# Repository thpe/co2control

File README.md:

# CO2 control
Monitor for CO2
## Features
 * EIA-485 interface
 * SCD-30 sensor
 * Input volatage 24 V
 * RP-2040
 * 4 LEDs
 * Relay
 * Oxygen Cell input < 150 mV (not yet tested)
 * 0-10 V output
 * 1 wire interface

## Issues and Limitations
The following issues with the current versions are known:
 * RX/TX to SCD30 need to be switched
 * doesn't connect via USB
   * USB C symbol should have been a receptable, not plug
   * Thus, B7/B6 are not connected to D+/-

## Connection
XLR male, pinout
 * 1. GND, Blue
 * 2. +24V, Blue/White
 * 3. 485A, Orange
 * 4. 485B, Orange/White

## Firmware
The [co2control-fw](https://github.com/thpe/co2control-fw) firmware samples the SCD-30 regulary and exposes the measurements via
modbus.

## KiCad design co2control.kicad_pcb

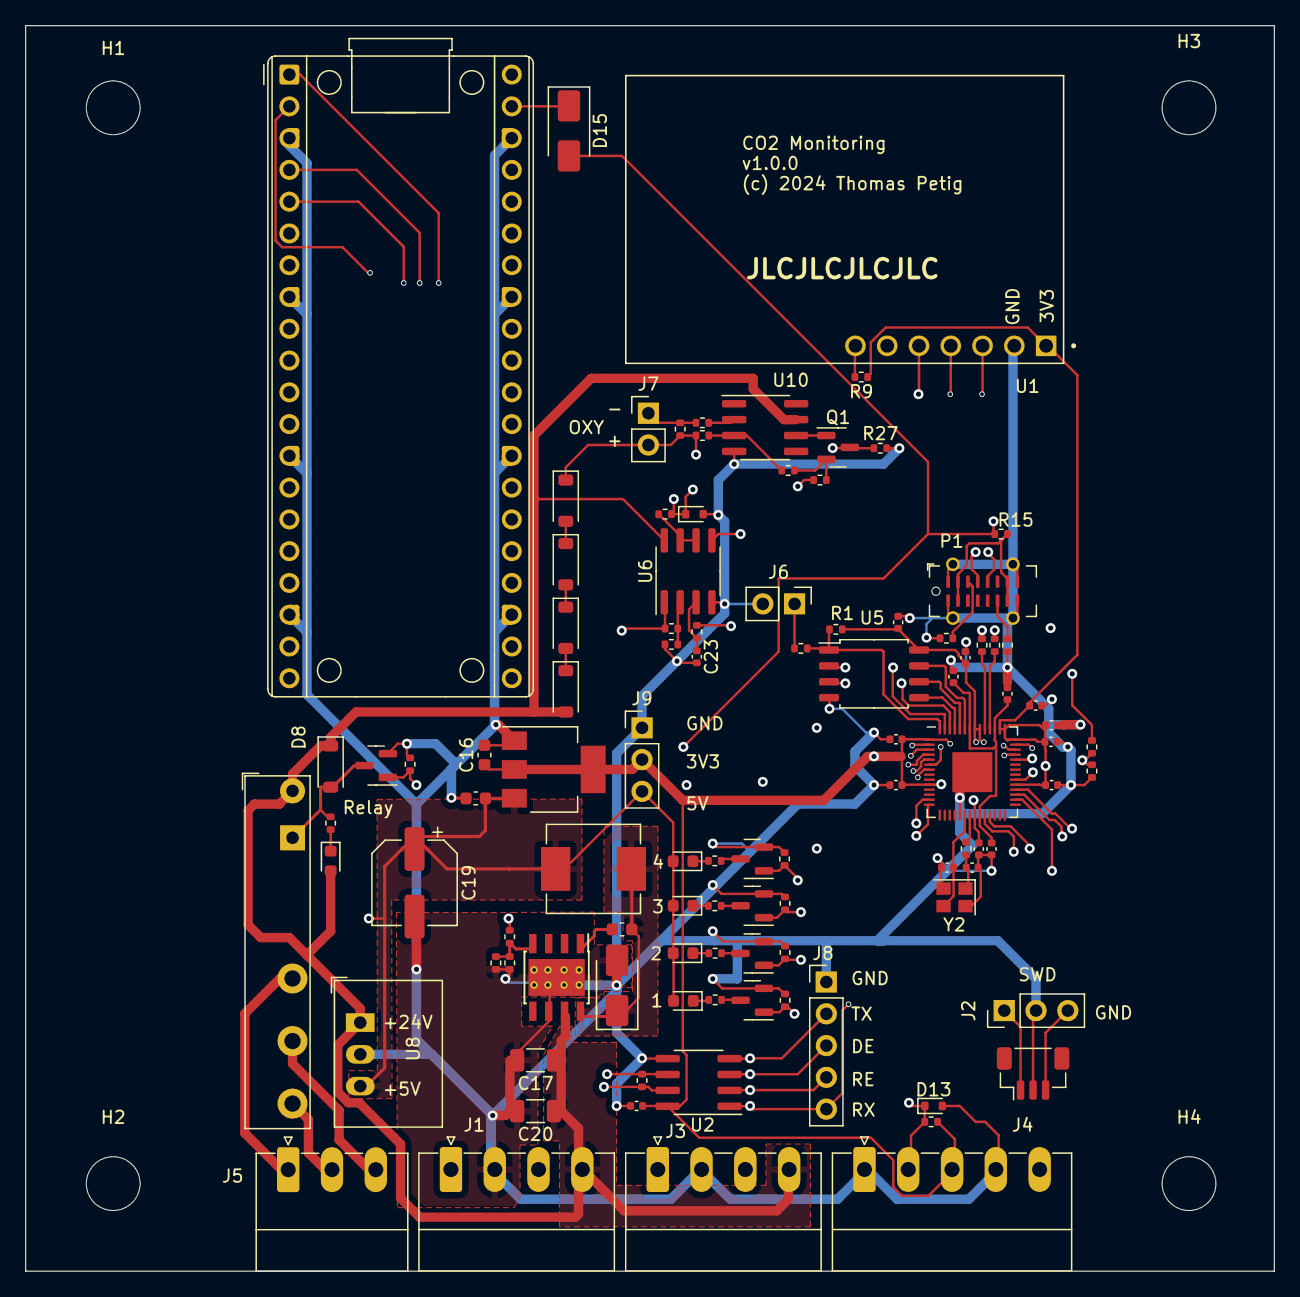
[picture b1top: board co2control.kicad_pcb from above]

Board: 4 copper layers, 99.8 x 99.6 mm, 106 parts (0 on the bottom side), 74 nets.

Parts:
C1, C4, C5, C6, C7, C8, C9, C10, C11, C12: 100n; C_0402_1005Metric
C2, C3, C23: 10p; C_0402_1005Metric
C13, C14: 1u; C_0402_1005Metric
C15, C16: 10u; C_0603_1608Metric
C17, C20: 4u7, 50V; C_1206_3216Metric
C18: 10n; C_0603_1608Metric
C19: 220u; CP_Elec_6.3x7.7
C21: 10n; C_0402_1005Metric
D2, D15: B340; D_SMA
D3, D4, D5, D6, D14: LED; LED_0603_1608Metric
D7, D8, D9, D10, D11: 1N4148W; D_SOD-123
D12, D13: MM5Z3V9; D_SOD-523
H1: MountingHole; MountingHole_4.3mm_M4_DIN965
H2, H3, H4: MountingHole; MountingHole_4.3mm_M4
J1, J3: Conn_01x04; PhoenixContact_MC_1,5_4-G-3.5_1x04_P3.50mm_Horizontal
J2: Conn_01x03_Pin; PinHeader_1x03_P2.54mm_Vertical
J4: Conn_01x05; PhoenixContact_MC_1,5_5-G-3.5_1x05_P3.50mm_Horizontal
J5: Conn_01x03; PhoenixContact_MC_1,5_3-G-3.5_1x03_P3.50mm_Horizontal
J6, J7: Conn_01x02; PinHeader_1x02_P2.54mm_Vertical
J8: Conn_01x05; PinHeader_1x05_P2.54mm_Vertical
J9: Conn_01x03; PinHeader_1x03_P2.54mm_Vertical
J10: Conn_01x03_Pin; JST_SH_BM03B-SRSS-TB_1x03-1MP_P1.00mm_Vertical
K1: Relay_SPDT; Relay_SPDT_Finder_34.51_Vertical
L1: 22u; L_Sunlord_MWSA0603S
P1: USB_C_Plug_USB2.0; USB_C_Receptacle_G-Switch_GT-USB-7051x
Q1: Q_PMOS_GSD; SOT-23
Q2, Q3, Q4, Q5, Q6: BSS138; SOT-23
R1, R15: DNF; R_0402_1005Metric
R2, R3, R16: 1k; R_0402_1005Metric
R4, R5: 27; R_0402_1005Metric
R6: 120; R_0402_1005Metric
R7, R9, R17, R19, R20, R27, R32, R33: 10k; R_0402_1005Metric
R8: 3k3; R_0402_1005Metric
R10, R12, R13, R30: 220; R_0402_1005Metric
R11, R22, R25, R26, R28, R29, R31, R36: 100k; R_0402_1005Metric
R14: 1M; R_0402_1005Metric
R18: 1k5; R_0402_1005Metric
R21: 4k7; R_0402_1005Metric
R23, R24: 330; R_0402_1005Metric
R34, R35: 5k1; R_0402_1005Metric
U1: SCD30; MODULE_SCD30
U2: SP3485EN; SOIC-8_3.9x4.9mm_P1.27mm
U3: AP1117-33; SOT-223-3_TabPin2
U4: RP2040; QFN-56-1EP_7x7mm_P0.4mm_EP3.2x3.2mm
U5: W25Q128JVS; SOIC-8_5.23x5.23mm_P1.27mm
U6: LM358; SOIC-8_3.9x4.9mm_P1.27mm
U7: RaspberryPi_Pico; RaspberryPi_Pico_Common_THT
U8: R-78C5.0-1.0; Converter_DCDC_RECOM_R-78E-0.5_THT
U9: TPS5430DDA; TI_SO-PowerPAD-8_ThermalVias
U10: OP07; SOIC-8_3.9x4.9mm_P1.27mm
Y2: 7E12000E10UCG; Crystal_SMD_2520-4Pin_2.5x2.0mm

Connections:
+1V1: C11.1, C12.1, C14.1, U4.23 (DVDD), U4.45 (VREG_VOUT), U4.50 (DVDD)
+3.3V: C1.1, C4.1, C5.1, C6.1, C7.1, C8.1, C9.1, C10.1, C13.1, C16.1, C21.1, J4.3, J9.2, R1.1, R9.1, R17.2, U1.1 (VDD), U2.8 (VCC), U3.2 (VO), U4.1 (IOVDD), U4.10 (IOVDD), U4.22 (IOVDD), U4.33 (IOVDD), U4.42 (IOVDD), U4.43 (ADC_AVDD), U4.44 (VREG_IN), U4.48 (USB_VDD), U4.49 (IOVDD), U5.8 (VCC)
+5V: C15.1, C19.1, D3.2 (A), D4.2 (A), D5.2 (A), D6.2 (A), D15.2 (A), J9.3, L1.2, R7.1, R15.2, R32.1, U3.3 (VI), U8.3 (OUT)
+24V: C17.1, C20.1, D7.2 (A), D8.1 (K), D14.2 (A), J1.4, J3.4, K1.A2, U6.8 (V+), U8.1 (IN), U9.7 (VIN), U10.7 (V+)
/io/1wire: D13.1 (K), J4.2, R17.1, U4.14 (GPIO11), U7.15 (GPIO11)
/io/485A: J1.1, J3.1, R6.1, U2.6 (A)
/io/485B: J1.3, J3.3, R6.2, U2.7 (B)
/io/MODBUS_DE: J8.3, U2.3 (DE), U4.4 (GPIO2), U7.4 (GPIO2)
/io/MODBUS_RE: J8.4, U2.2 (~RE), U4.5 (GPIO3), U7.5 (GPIO3)
/io/MODBUS_RX: J8.5, U2.1 (RO), U4.3 (GPIO1), U7.2 (GPIO1)
/io/MODBUS_TX: J8.2, U2.4 (DI), U4.2 (GPIO0), U7.1 (GPIO0)
/io/OUT1_10V: J4.5, R19.1, U6.1
/io/PWM1: R21.2, U4.13 (GPIO10), U7.14 (GPIO10)
/io/RELAY: Q2.1 (G), R22.2, U4.39 (GPIO27_ADC1), U7.32 (GPIO27_ADC1)
/io/Voxy: D12.1 (K), R16.1, U4.38 (GPIO26_ADC0), U7.31 (GPIO26_ADC0)
/power/PH: C18.2, D2.1 (K), L1.1, U9.8 (PH)
/processing/ADC2: U1.5 (RDY), U4.40 (GPIO28_ADC2), U7.34 (GPIO28_ADC2)
/processing/LED1: Q6.1 (G), R31.2, U4.30 (GPIO19), U7.25 (GPIO19)
/processing/LED2: Q4.1 (G), R11.2, U4.31 (GPIO20), U7.26 (GPIO20)
/processing/LED3: Q5.1 (G), R29.2, U4.32 (GPIO21), U7.27 (GPIO21)
/processing/LED4: Q3.1 (G), R28.2, U4.34 (GPIO22), U7.29 (GPIO22)
/processing/UART1 RX: U1.4 (RX/SDA), U4.7 (GPIO5), U7.7 (GPIO5)
/processing/UART1 TX: U1.3 (TX/SCL), U4.6 (GPIO4), U7.6 (GPIO4)
/processing/USB_D+: P1.A6 (D+), R5.1
/processing/USB_D-: P1.A7 (D-), R4.2
GND: C1.2, C2.1, C3.1, C4.2, C5.2, C6.2, C7.2, C8.2, C9.2, C10.2, C11.2, C12.2, C13.2, C14.2, C15.2, C16.2, C17.2, C19.2, C20.2, C21.2, C23.2, D2.2 (A), D12.2 (A), D13.2 (A), J1.2, J2.2, J3.2, J4.1, J4.4, J6.2, J8.1, J9.1, J10.2, P1.A1 (GND), P1.A12 (GND), P1.B1 (GND), P1.B12 (GND), P1.S1 (SHIELD), Q2.2 (S), Q3.2 (S), Q4.2 (S), Q5.2 (S), Q6.2 (S), R8.2, R11.1, R20.1, R22.1, R27.2, R28.1, R29.1, R31.1, R33.2, R34.1, R35.1, R36.2, U1.2 (GND), U2.5 (GND), U3.1 (GND), U4.19 (TESTEN), U4.57 (GND), U5.4 (GND), U6.4 (V-), U7.3 (GND), U7.8 (GND), U7.13 (GND), U7.18 (GND), U7.23 (GND), U7.28 (GND), U7.33 (AGND), U7.38 (GND), U8.2 (GND), U9.6 (GND), U9.9 (GNDPAD), U10.4 (V-), Y2.2, Y2.4
unnamed: C3.2, R3.1, Y2.1
unnamed: D3.1 (K), R10.1
unnamed: D4.1 (K), R12.1
unnamed: D5.1 (K), R30.1
unnamed: D6.1 (K), R13.1
unnamed: D7.1 (K), D9.2 (A)
unnamed: D8.2 (A), K1.A1, Q2.3 (D), R18.2
unnamed: D9.1 (K), D10.2 (A)
unnamed: D10.1 (K), D11.2 (A)
unnamed: D11.1 (K), J7.2, R14.1, R23.1, R26.1
unnamed: D14.1 (K), R18.1
unnamed: D15.1 (K), U7.39 (VSYS)
unnamed: J5.1, K1.12
unnamed: J5.2, K1.14
unnamed: J5.3, K1.11
unnamed: J6.1, R2.1
unnamed: J7.1, R14.2, R24.1
unnamed: J2.1, J10.1, U4.24 (SWCLK)
unnamed: J2.3, J10.3, U4.25 (SWD)
unnamed: P1.A5 (CC), R34.2
unnamed: P1.A4 (VBUS), P1.A9 (VBUS), P1.B4 (VBUS), P1.B9 (VBUS), R15.1
unnamed: P1.B5 (VCONN), R35.2
unnamed: Q1.3 (D), R27.1, U6.5 (+)
unnamed: Q1.1 (G), U10.6
unnamed: Q1.2 (S), R25.2, R26.2
unnamed: Q3.3 (D), R13.2
unnamed: Q4.3 (D), R10.2
unnamed: Q5.3 (D), R12.2
unnamed: Q6.3 (D), R30.2
unnamed: R9.2, U1.7 (SEL)
unnamed: R32.2, R33.1, U4.41 (GPIO29_ADC3)
unnamed: U4.52 (QSPI_SCLK), U5.6 (CLK)
unnamed: U4.53 (QSPI_SD0), U5.5 (DI(IO0))
unnamed: U4.55 (QSPI_SD1), U5.2 (DO(IO1))
unnamed: U4.54 (QSPI_SD2), U5.3 (IO2)
unnamed: U4.51 (QSPI_SD3), U5.7 (IO3)
unnamed: R1.2, R2.2, U4.56 (QSPI_SS), U5.1 (~CS)
unnamed: R4.1, U4.46 (USB_DM)
unnamed: R5.2, U4.47 (USB_DP)
unnamed: C2.2, U4.20 (XIN), Y2.3
unnamed: R3.2, U4.21 (XOUT)
unnamed: C23.1, R21.1, U6.3 (+)
unnamed: R19.2, R20.2, U6.2 (-)
unnamed: R16.2, U6.6 (-), U6.7
unnamed: C18.1, U9.1 (BOOT)
unnamed: R7.2, R8.1, R36.1, U9.4 (VSENSE)
unnamed: R23.2, R25.1, U10.3 (+)
unnamed: R24.2, U10.2 (-)

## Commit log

2024-03-07 added board
2024-03-07 added picture
2024-03-22 added some issues
2024-07-29 Update README.md
    add more detail on USB issues
2024-07-29 Update README.md
    add right indention
2024-08-29 add link to firmware
2025-03-06 add some detail on the external connection

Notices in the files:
co2control.kicad_pcb:
(c) 2024 Thomas Petig
